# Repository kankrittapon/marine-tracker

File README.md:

# Marine Tracker V1 — Electrical Design Package

Status: Rev A architecture and connection specification. **Not released for fabrication.**

## Frozen architecture

- U1: SIMCom A7670SA, LTE Cat-1, intended OpenCPU host
- U2: Quectel LC29H-AA, L1/L5 dual-band GNSS
- No ESP32 and no external application MCU
- 1-cell protected Li-ion/LiPo battery
- USB-C charging/service
- External LTE and active dual-band GNSS antennas
- Four-layer controlled-impedance PCB

## Sheet structure for schematic capture

1. `POWER`: USB-C protection, BQ24074 power-path charger, battery/NTC, A7670 rail and low-noise GNSS rail
2. `CELLULAR`: A7670SA, PWRKEY/reset/status, UART/USB test access and LTE RF matching
3. `SIM`: nano-SIM, low-capacitance ESD and optional MFF2 eSIM pads
4. `GNSS`: LC29H-AA, UART/PPS level translation, reset, backup supply and active antenna bias/filter
5. `SERVICE`: LEDs (DNP for low-power build), test points and expansion header

## Fixed electrical decisions

- A7670 VBAT connects to the charger SYS/battery domain through a ferrite bead or 0-ohm current-rated link. Route for at least 3 A transient capability.
- Place 1000 uF low-ESR polymer, 100 uF, 10 uF and 100 nF at A7670 VBAT. Final values must be reconciled against the exact A7670SA hardware revision reference design.
- LC29H receives a dedicated low-noise 3.3 V rail from TPS7A2033. Do not share its decoupling path with the LTE modem.
- LC29H UART1 is the navigation interface; UART2 remains available at test pads for firmware/debug.
- LC29H D_SEL1/D_SEL2 receive explicit straps after confirming the UART selection truth table in the current module datasheet. They must not float.
- LC29H active antenna feed uses 68 nH bias inductance, 10-ohm short protection, 100 pF DC block and a C-L-C matching reservation.
- Reserve B39162B2651P810 dual-band GNSS SAW footprint immediately before LC29H RF_IN. Confirm insertion loss and availability before assembly.
- LTE and GNSS feeds are 50 ohm controlled impedance. Antennas must demonstrate at least 20 dB isolation in the final enclosure.
- USB D+/D- are 90-ohm differential, length matched, with ESD at the connector.

## Release blockers

1. Exact A7670SA OpenCPU hardware revision, SDK and pin-multiplex table
2. A7670SA official symbol/footprint cross-check
3. Enclosure outline, mounting holes and connector locations
4. Battery capacity, connector and NTC curve
5. LTE/GNSS antenna part numbers and cable lengths
6. Quectel/SIMCom design review
7. ERC, PCB DRC, impedance calculation, RF tuning and enclosure test

The files in this directory are deliberately marked Rev A. They document every required circuit and net, but fabrication outputs must not be generated until the release blockers are closed.

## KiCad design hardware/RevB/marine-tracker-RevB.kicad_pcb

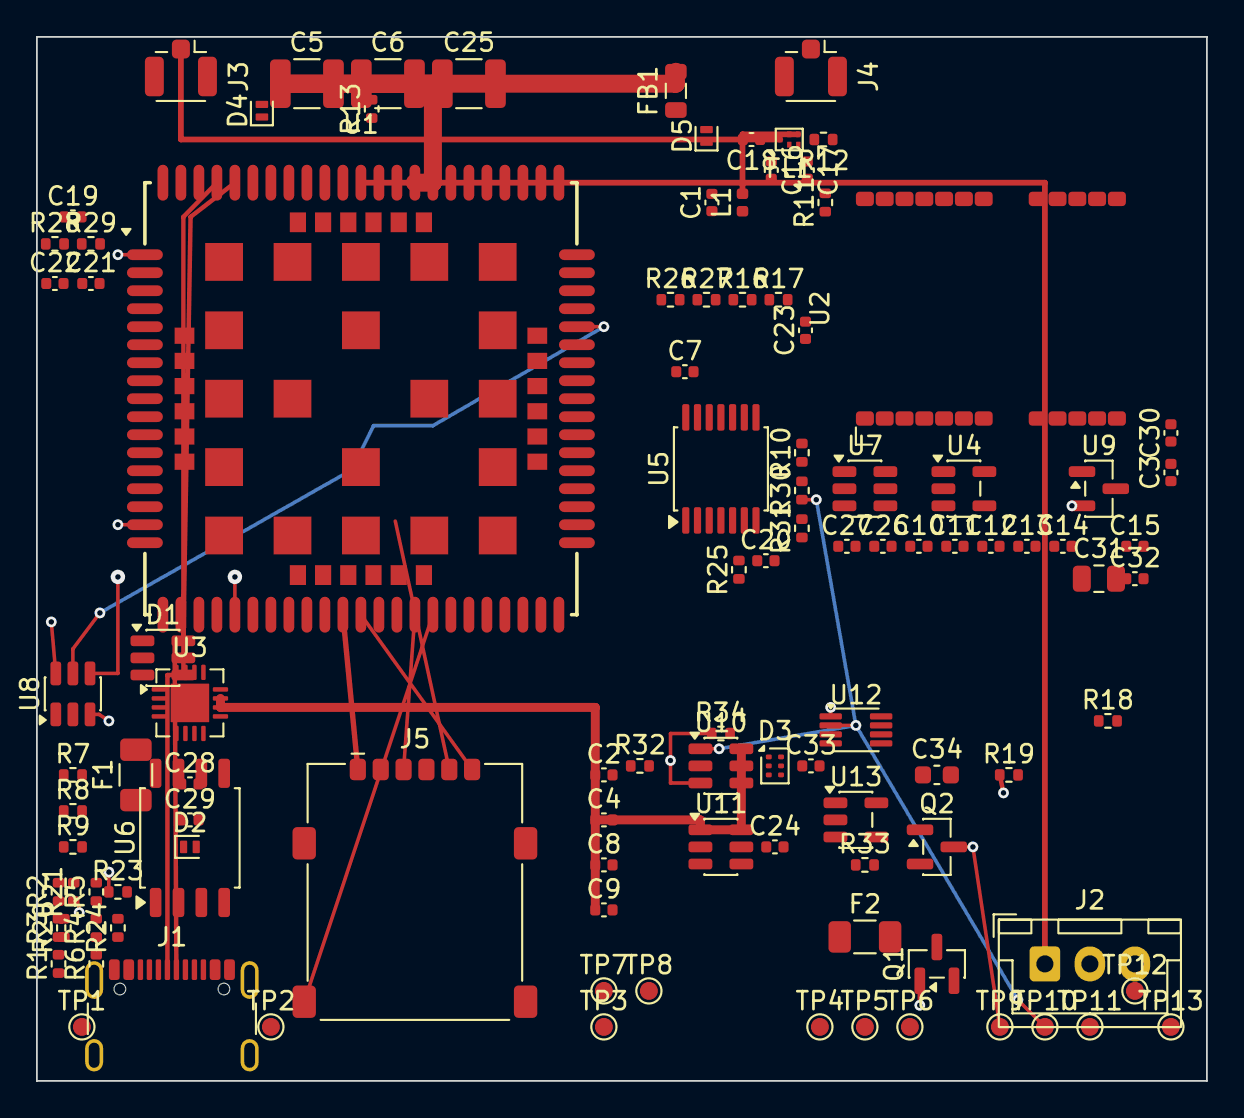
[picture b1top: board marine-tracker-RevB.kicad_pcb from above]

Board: 4 copper layers, 65.0 x 58.0 mm, 108 parts (0 on the bottom side), 77 nets.

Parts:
C1, C4, C9, C12: 10u; C_0402_1005Metric
C2, C8, C11, C13, C19, C20, C21, C23, C24, C28, C29: 100n; C_0402_1005Metric
C3, C15: 4.7u; C_0402_1005Metric
C5, C6, C25: 100u_LOW_ESR; C_1210_3225Metric
C7, C10, C22, C27: 1u; C_0402_1005Metric
C14: 33p_C0G; C_0402_1005Metric
C16, C17: DNP_RF_MATCH; C_0402_1005Metric
C18: 100p_C0G; C_0402_1005Metric
C26: 1n_C0G; C_0402_1005Metric
C30, C32, C33: 0.1uF; C_0402_1005Metric
C31: 1uF_C0G; C_0805_2012Metric
C34: 1uF_X7R; C_0603_1608Metric
D1: USBLC6-2SC6; SOT-23-6
D2: PESD5V0S1UL; D_SOD-882
D3: PESD5V0L4UF; SOT-886
D4: LTE_RF_ESD_DNP; D_SOD-882
D5: GNSS_RF_ESD; D_SOD-882
F1: 1.1A_PTC; Fuse_1206_3216Metric
F2: 2.0A_PTC_BAT; Fuse_1206_3216Metric
FB1: 600R@100MHz/0R_ALT; L_0805_2012Metric
FL1: B39162B2651P810; Filter_1411-5_1.4x1.1mm
J1: USB-C; USB_C_Receptacle_GCT_USB4105-xx-A_16P_TopMnt_Horizontal
J2: BATTERY; JST_XH_B3B-XH-A_1x03_P2.50mm_Vertical
J3: LTE_U.FL; U.FL_Hirose_U.FL-R-SMT-1_Vertical
J4: GNSS_L1_L5_U.FL; U.FL_Hirose_U.FL-R-SMT-1_Vertical
J5: Nano_SIM; nanoSIM_GCT_SIM8060-6-1-14-00
L1: 68nH; L_0402_1005Metric
Q1: AO3401A_REVERSE_POLARITY; SOT-23
Q2: MMBT2222A; SOT-23
R1, R2: 5.1k; R_0402_1005Metric
R3: 1.13k; R_0402_1005Metric
R4: 1.18k; R_0402_1005Metric
R5: 4.12k; R_0402_1005Metric
R6: 46.4k; R_0402_1005Metric
R7, R8, R12, R13: 0R; R_0402_1005Metric
R9: 10k_DNP; R_0402_1005Metric
R10, R20, R28, R29, R33: 10k; R_0402_1005Metric
R11: 10R; R_0402_1005Metric
R16: 1M; R_0402_1005Metric
R17: 330k; R_0402_1005Metric
R18: 1k; R_0402_1005Metric
R19, R24, R25, R34: 100k; R_0402_1005Metric
R21: 124k_1%; R_0402_1005Metric
R23: 107k_1%; R_0402_1005Metric
R26: 680k_1%; R_0402_1005Metric
R27: 470k_1%; R_0402_1005Metric
R30: 100k_1%; R_0402_1005Metric
R31: 6.19k_1%; R_0402_1005Metric
R32: 150k_1%; R_0402_1005Metric
TP1: TP_USB_VBUS_RAW; TestPoint_Pad_D1.0mm
TP2: TP_USB_VBUS_FUSED; TestPoint_Pad_D1.0mm
TP3: TP_BAT_PACK_POS; TestPoint_Pad_D1.0mm
TP4: TP_BAT_CELL; TestPoint_Pad_D1.0mm
TP5: TP_VBAT_MODEM; TestPoint_Pad_D1.0mm
TP6: TP_VSYS; TestPoint_Pad_D1.0mm
TP7: TP_GNSS_3V3; TestPoint_Pad_D1.0mm
TP8: TP_VDD_1V8; TestPoint_Pad_D1.0mm
TP9: TP_PWRKEY; TestPoint_Pad_D1.0mm
TP10: TP_MODEM_RESET_N; TestPoint_Pad_D1.0mm
TP11: TP_CELL_TX_A; TestPoint_Pad_D1.0mm
TP12: TP_CELL_RX_A; TestPoint_Pad_D1.0mm
TP13: TP_GND; TestPoint_Pad_D1.0mm
U1: A7670G-LABE; A7670G_LABE_124
U2: LC29H-AA; LC29H_24LCC
U3: BQ24074RGTR; Texas_RVA_VQFN-16-1EP_3.5x3.5mm_P0.5mm_EP2.14x2.14mm
U4: TPS7A2033PDBV; SOT-23-5
U5: TXS0104EPW; TSSOP-14_4.4x5mm_P0.65mm
U6: W25Q32JWSSIM; SOIC-8_5.3x5.3mm_P1.27mm
U7: TPS22917DBV_GNSS_LOAD; SOT-23-6
U8: TPL5010_10MIN_WATCHDOG; SOT-23-6
U9: TPS3839K33DBZR; SOT-23
U10: TPS3808G09DBVR; SOT-23-6
U11: TPL5111DDCR; SOT-23-6
U12: SN74LVC2G08DCUR; VSSOP-8_2.3x2mm_P0.5mm
U13: SN74LVC1G14DBVR; SOT-23-5

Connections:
AUTO_PWRKEY_BASE: Q2.1, R33.2
AUTO_PWRKEY_DRV: R33.1, U11.5
BAT_CELL: C3.1, F2.2, R16.1, TP4.1, U3.2, U3.3
BAT_GATE: Q1.1, R19.1
BAT_PACK_POS: J2.1, Q1.3, TP3.1
BAT_PROTECTED: F2.1, Q1.2
BAT_SENSE: C23.1, R16.2, R17.1
CELL_RX_A: TP12.1, U1.49, U5.3
CELL_TX_A: TP11.1, U1.50, U5.2
CHG_EN1: R8.1, U3.6
CHG_EN2: R7.1, U3.5
CHG_PGOOD: R20.1, U1.53, U3.7
CHG_STATUS: R24.1, U1.48, U3.9
CHG_TS: J2.2, R9.1, U3.1
FLASH_3V3: C21.1, C22.1
FLASH_CS_N: U1.12, U6.1
FLASH_HOLD_N: R29.2, U6.7
FLASH_MISO: U1.14, U6.2
FLASH_MOSI: U1.13, U6.5
FLASH_SCK: U1.11, U6.6
FLASH_WP_N: R28.2, U6.3
GND: C2.2, C3.2, C4.2, C5.2, C6.2, C7.2, C8.2, C9.2, C10.2, C11.2, C12.2, C13.2, C14.2, C15.2, C19.2, C20.2, C21.2, C22.2, C23.2, C24.2, C25.2, C26.2, C27.2, C28.2, C29.2, C30.2, C31.2, C32.2, C33.2, C34.2, D1.2, D2.2, D3.2, D3.5, D4.2, D5.2, FL1.2, J1.A1, J1.A12, J1.B1, J1.B12, J1.SH, J2.3, J3.2, J4.2, J5.5, J5.SH, Q2.2, R1.2, R2.2, R3.2, R4.2, R5.2, R6.2, R8.2, R9.2, R10.2, R17.2, R19.2, R21.2, R23.2, R27.2, R31.2, TP13.1, U1.2, U1.17, U1.18, U1.29, U1.39, U1.45, U1.46, U1.54, U1.58, U1.59, U1.61, U1.62, U1.63, U1.64, U1.65, U1.69, U1.70, U1.71, U1.72, U1.73, U1.74, U1.75, U1.76, U1.77, U1.78, U1.79, U1.80, U1.81, U1.82, U1.83, U1.84, U1.85, U1.86, U1.87, U1.88, U1.91, U1.92, U1.94, U2.5, U2.6, U2.10, U2.12, U2.13, U2.24, U3.4, U3.8, U3.17, U4.2, U5.7, U6.4, U7.2, U8.2, U9.1, U10.2, U11.2, U11.4, U11.6, U12.4, U13.3
GNSS_2V8_IO: C20.1, U2.7, U5.14
GNSS_3V3: C10.1, C11.1, C12.1, C13.1, C14.1, R18.1, R25.2, TP7.1, U2.23, U4.5
GNSS_BIAS_LIMITED: C1.1, L1.1, R11.2
GNSS_BIAS_SRC: R11.1, U2.9
GNSS_PPS_A: U1.100, U5.5
GNSS_PPS_B: U2.3, U5.10
GNSS_PWR_EN: U1.26, U7.3
GNSS_RESET_B: U2.8, U5.11
GNSS_RF: R12.2, U2.11
GNSS_RF_CONN: C1.2, C18.1, D5.1, J4.1, L1.2
GNSS_RF_FILTER_IN: C18.2, FL1.1
GNSS_RF_FILTER_OUT: FL1.3, R12.1
GNSS_RX_B: U2.21, U5.13
GNSS_SW_CT: C26.1, U7.4
GNSS_SW_IN: C27.1, U4.1, U4.3, U7.5, U7.6
GNSS_TX_B: U2.20, U5.12
GNSS_VBACKUP: C15.1, U2.22
GNSS_WAKE_B: R25.1, U2.1
ILIM_SET: R4.1, U3.12
ISET_SET: R3.1, U3.16
ITERM_SET: R5.1, U3.15
LEVEL_OE: R10.1, U5.8
LTE_RF: R13.1, U1.60
LTE_RF_CONN: D4.1, J3.1, R13.2
MODEM_RESET_N: R30.1, TP10.1, U1.16, U10.1, U12.2
PWRKEY: Q2.3, TP9.1, U1.1
PWRKEY_ARM: R32.1, U12.5, U12.7
PWRKEY_ARM_DLY: C34.1, R32.2, U13.2
PWRKEY_ARM_DLY_N: U12.6, U13.4
PWRKEY_TRIG: R31.1, U11.3, U12.3
PWR_FLAG: R18.2, U1.24, U1.55, U1.89
SIM_CLK: D3.3, J5.3, U1.32
SIM_DATA: D3.6, J5.7, U1.31
SIM_DET: J5.SW, U1.34
SIM_RST: D3.1, J5.2, U1.33
SIM_VDD: C24.1, D3.4, J5.1, U1.30
STRETCH_CT: C31.1, U10.4
SUPV_TRIG: U9.2, U12.1
TMR_SET: R6.1, U3.14
USB_CC1: J1.A5, R1.1
USB_CC2: J1.B5, R2.1
USB_DM_CONN: D1.3, J1.A7, J1.B7
USB_DM_MODEM: D1.4, U1.28
USB_DP_CONN: D1.1, J1.A6, J1.B6
USB_DP_MODEM: D1.6, U1.27
USB_VBUS_FUSED: C2.1, C8.1, D1.5, F1.2, R7.2, TP2.1, U3.13
USB_VBUS_RAW: D2.1, F1.1, J1.A4, J1.A9, J1.B4, J1.B9, TP1.1
VBAT_ADC_SENSE: R26.2, R27.1, U1.51
VBAT_MODEM: C5.1, C6.1, C25.1, FB1.2, R26.1, TP5.1, U1.56, U1.57
VDD_1V8: C7.1, C19.1, C28.1, C29.1, R20.2, R24.2, R28.1, R29.1, TP8.1, U1.15, U5.1, U6.8, U8.1
VSYS: C4.1, C9.1, C30.1, C32.1, C33.1, FB1.1, R30.2, R34.2, TP6.1, U3.10, U3.11, U7.1, U9.3, U10.5, U10.6, U11.1, U12.8, U13.5
WDT_DELAY: R21.1, R23.1, U8.3
WDT_DONE: U1.19, U8.4
WDT_RST_TRIG: R34.1, U8.6, U10.3
WDT_WAKE: U1.47, U8.5
